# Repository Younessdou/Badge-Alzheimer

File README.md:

# Badge-Alzheimer
Projet électronique du semestre 5

# Sommaire 
### Introduction
### I) Cahier des charges
### II) Gantt et diagramme d'architecture
### III) Choix des composants
##### A) Module GPS
##### B) Module Lora
##### C) Microprocesseur
### IV) Réalisation du PCB
##### A) Choix des pins du microP
##### B) Schématic & board
##### C) Soudage des composants sur la carte
### V) Codage du module GPS 
### VI) LoRa
### VII) Alimentation
### Conclusion

# Remerciement
Nous remercions nos tuteurs durant ce projet Mr.Papazoglou et Mme.Giannini pour leurs conseils et astuces qui nous ont permis de découvrir de nouvelles choses et acquérir de nouvelles compétences tout en appliquant ce que nous avions vu durant cette année d'étude, et nous tenons aussi à remercier Mme. Kittel du bureau technique qui nous a aidé pour notre PCB.
# Introduction
Dans le cadre des projets tutorés du semestre 6, nous avons été amenés à travailler sur la conception d’un badge Alzheimer qu’on a choisi de le nommer «TrackNanny».
TrackNanny est tout simplement un outil de localisation et de prévention, destiné aux personnes atteintes d’Alzheimer ou aux personnes qu’on ne souhaiterait pas perdre à l’extérieur. Ce badge permet d’envoyer une alerte à la personne qui prend en charge l’utilisateur dès que ce dernier dépasse un rayon prédéfini par rapport à un épicentre qui est aussi prédéfini. Ce badge contient aussi un bouton SOS qui permet d’envoyer un autre message d’alerte avec la position exacte de l’utilisateur si quelqu’un l’a trouvé.
Pour notre projet on a pris l'adresse de l'ENSEA comme épicentre et on a défini un rayon de 700m.       
    <p align="center">
  
### Gantt & diagramme d’architecture
Durant ces 11 séances de projets, nous avons commencé par répartir les tâches entres nous en remplissant notre diagramme de Gantt où on a placé nos missions par ordre de priorité.

Et on a structuré notre projet selon le diagramme d'architecture suivant:

# I) Cahier des charges
Pendant la première séance nous avons commencé par établir un cahier des charges sur lequel on s'est basé pour la suite du projet:
    <p align="center">

    Budget: 50€
# III) Choix des composants
### A) Module GPS
      Module GPS : SKU:TEL0132

 ### B) Module LORA
   Module LoRa-E5 Grove 113020091\

On a choisi le module LoRa-E5 Grove 113020091 puisque c'était le moins cher et le plus compacte par rapport aux autres.
  
 ### C) Microprocesseur
     STM32L412KBT6

tableau des microprocesseurs proposés:

  Au début on avait le choix entre 4 microprocesseurs, et puisqu’on va utiliser 2 UART et 1 GPIO; 1 pour le module GPS et 1 pour le LoRa, donc il nous restait 2 choix et puisque le STM32L021K4T6 n'est pas toujours fiable , on a opté pour le 4ème vu son prix qui est presque la moitié du 3ème et aussi puisqu’il a le même package que les autres donc on aura la possibilité de le changer sur notre PCB et aussi puisqu’il contient que 32 pin et ça reste plus simple et facile à souder et manipuler que celui avec 64 pins.

# IV) Réalisation du PCB
        
 ### A) Choix des pins du microP
Nous avons fait bon usage du Logiciel STM32CubeIDE afin de voir les pins associés à l’UART, leurs numéros ainsi que leurs dispositions lors de la création de la carte Pcb.
Après ajout des pins pour notre bouton SOS et RESET, on se retrouve avec une Pin view comme ci-contre :

- Pin PA2-3 : Module GPS
- Pin PA5 : Bouton SOS
- Pin PA14-15 : RESET 
- Pin PA9-10 : Module LoRaWan   
        
 ### B) Schematic et board
 
 Nous avons commencé par créer notre PCB sur eagle en téléchargeant les librairies contenant nos composants, puis on a créé notre schématic qui contient la partie microP, l'alimentation les connecteurs pour le module GPS et LoRa ainsi que nos deux boutons reset et SOS.

  À partir de ce schématic on a généré notre board pour relier les composants entre eux en top ou en buttom.

  Après le routage de ce dernier, on a bien respecté notre objectif qui est de réduire l'espace entre les composants et mettre un grand nombre de liaison en top afin d'obtenir une carte adéquate avec la forme de notre badge, ensuite on l'a imprimé et on a soudé les composants dessus à l'aide de mr.Papazouglou et mme.Kittel.
 
 Voici le format final de notre PCB:

 # V) Codage du module GPS
 Cette partie a été faite par deux autres étudiants; Alexis Regnault et Valérian PRIOU qui se sont occupés de la partie software de plusieurs projets dont le nôtre, veuillez trouver leurs rapports pour notre projet ci-joint avec les fichiers, il est intitulé «Rapport_Alzheimer_PRIOU_REGNAULT.pdf» ainsi que le git du codage du module GPS via le lien ci-dessous.
https://github.com/ValerianPRIOU/Alzheimer
        
 # VI) LoRa or LoRaWAN?
 Cette partie a été géré par deux autres étudiants; Mohamed Amine Bouhyat Oliver BELLIARD ABREU, ils ont aussi travaillé sur la partie LoRawan des autres projets. Veuillez trouver le lien de leurs git ci-dessous.
        
  https://github.com/OliverBELLIARD/LoRaWAN     

 # VII) Alimentation:
 Cette partie a été géré par deux étudiantes; Inass Rachidi Manon COTTAR qui s'occupaient de l'alimentation de plusieurs projets en même temps, vous trouverez le lien ci-dessous du travail détaillé qui a été fait en parallèle avec nous.

https://github.com/inassra/batterie

# Conclusion
Pour le moment, nous n'avons toujours pas terminé notre projet, il nous reste dans la partie software l'assemblage du code du module GPS et le module LoRa dans un seul code qui doit être implémenter par la suite dans le microprocesseur, lors du test de notre carte on a eu un problème avec le régulateur qui délivre les 5V en revanche on obtient bien nos 6V à l'entrée ainsi que nos 3,3V à la sortie de l'autre régulateur. Ce premier projet a été très intéressant puisqu'on a pu appliquer la plupart des connaissances et compétences vu durant cette année. L'idée du projet est très intéressante et on peut poursuivre le travail sur ce projet après en essayant de le compléter et de l'améliorer en modifiant notre cahier des charges et en ajoutant d'autres missions comme un accéléromètre pour détecter la chute de l'utilisateur.

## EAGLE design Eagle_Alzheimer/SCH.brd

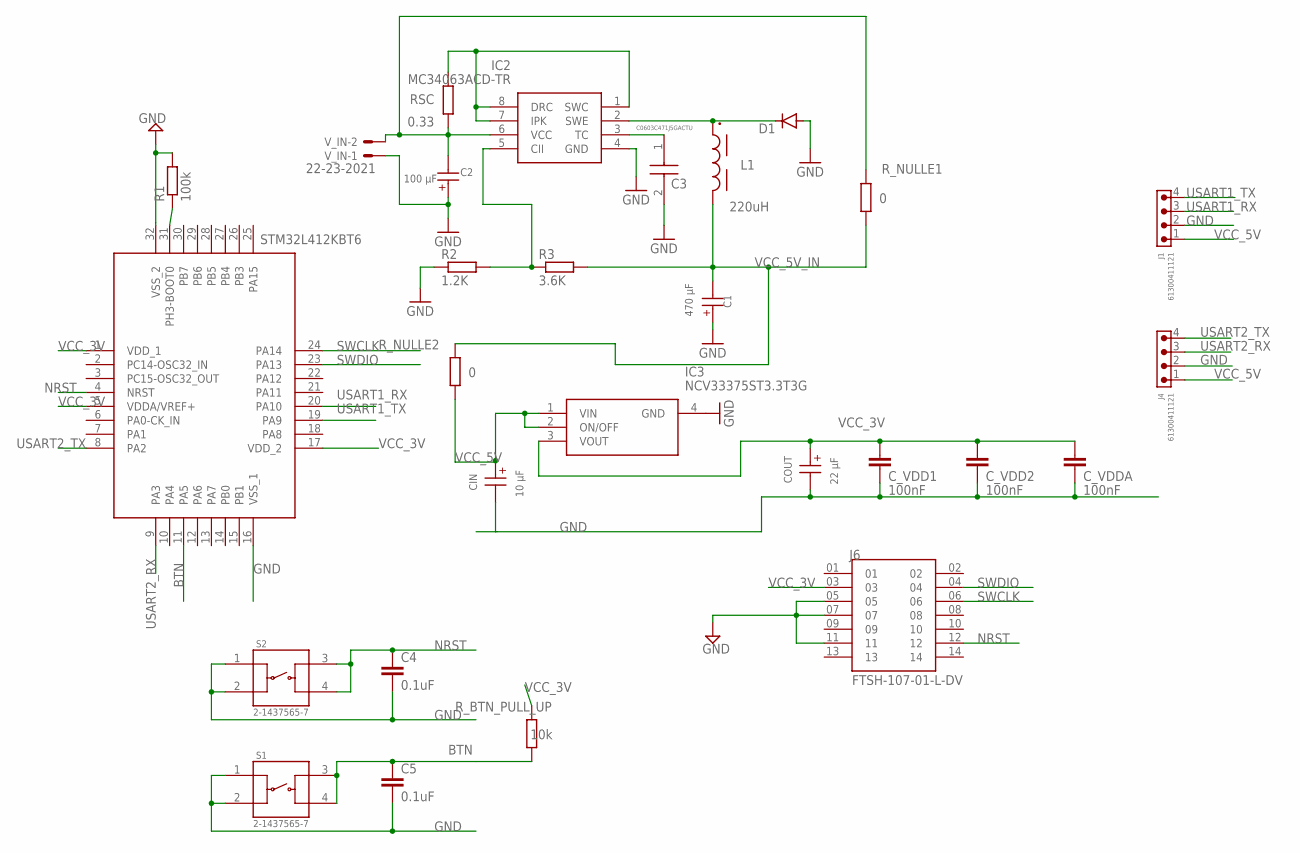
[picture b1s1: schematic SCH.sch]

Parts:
C1: 470 µF; WCAP-ASLL_8X10.5(DXL)
C2: 100 µF; WCAP-ASLL_6.3X7.7(DXL)
C3: C0603C471J5GACTU; C0603
C4, C5: 0.1uF; C0603
CIN: 10 µF; WCAP-ASLL_4X5.5(DXL)
COUT: 22 µF; WCAP-ASLL_5X5.5(DXL)
C_VDD1, C_VDD2: 100nF; C0603
C_VDDA: 100nF; C0603
D1: DIODE-DO214AC; DO214AC
IC1: STM32L412KBT6; QFP80P900X900X160-32N
IC2: MC34063ACD-TR; SOIC127P600X175-8N
IC3: NCV33375ST3.3T3G; SOT230P700X175-4N
J1, J4: 61300411121
J6: FTSH-107-01-L-DV; SAMTEC_FTSH-107-01-L-DV
L1: 220uH; WE-PDA_1260
R1: 100k; R0603
R2: 1.2K; R0603
R3: 3.6K; R0603
RSC: 0.33; R1206W
R_BTN_PULL_UP: 10k; R0603
R_NULLE1, R_NULLE2: 0; R0603
S1, S2: 2-1437565-7; SW_2-1437565-7
V_IN: 22-23-2021

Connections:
BTN: C5.1, IC1.11 (PA5), R_BTN_PULL_UP.1, S1.3, S1.4
GND: C1.1 (+), C2.1 (+), C3.2, C4.2, C5.2, CIN.2 (-), COUT.2 (-), C_VDD1.2, C_VDD2.2, C_VDDA.2, D1.A, IC1.16 (VSS_1), IC1.32 (VSS_2), IC2.4 (GND), IC3.4 (GND), J1.2, J4.2, J6.05, J6.07, J6.11, R1.2, R2.1, S1.1, S1.2, S2.1, S2.2, V_IN.1
unnamed: IC1.31 (PH3-BOOT0), R1.1
unnamed: IC2.1 (SWC), IC2.7 (IPK), IC2.8 (DRC), RSC.2
unnamed: IC2.5 (CII), R2.2, R3.1
unnamed: C3.1, IC2.3 (TC)
unnamed: D1.C, IC2.2 (SWE), L1.1
NRST: C4.1, IC1.4 (NRST), J6.12, S2.3, S2.4
SWCLK: IC1.24 (PA14), J6.06
SWDIO: IC1.23 (PA13), J6.04
USART1_RX: IC1.20 (PA10), J1.3
USART1_TX: IC1.19 (PA9), J1.4
USART2_RX: IC1.9 (PA3), J4.3
USART2_TX: IC1.8 (PA2), J4.4
VCC_3V: COUT.1 (+), C_VDD1.1, C_VDD2.1, C_VDDA.1, IC1.1 (VDD_1), IC1.5 (VDDA/VREF+), IC1.17 (VDD_2), IC3.3 (VOUT), J6.03, R_BTN_PULL_UP.2
VCC_5V: CIN.1 (+), IC3.1 (VIN), IC3.2 (ON/OFF), J1.1, J4.1, R_NULLE2.1
VCC_5V_IN: C1.2 (-), L1.2, R3.2, R_NULLE1.1, R_NULLE2.2
VCC_6V: C2.2 (-), IC2.6 (VCC), RSC.1, R_NULLE1.2, V_IN.2

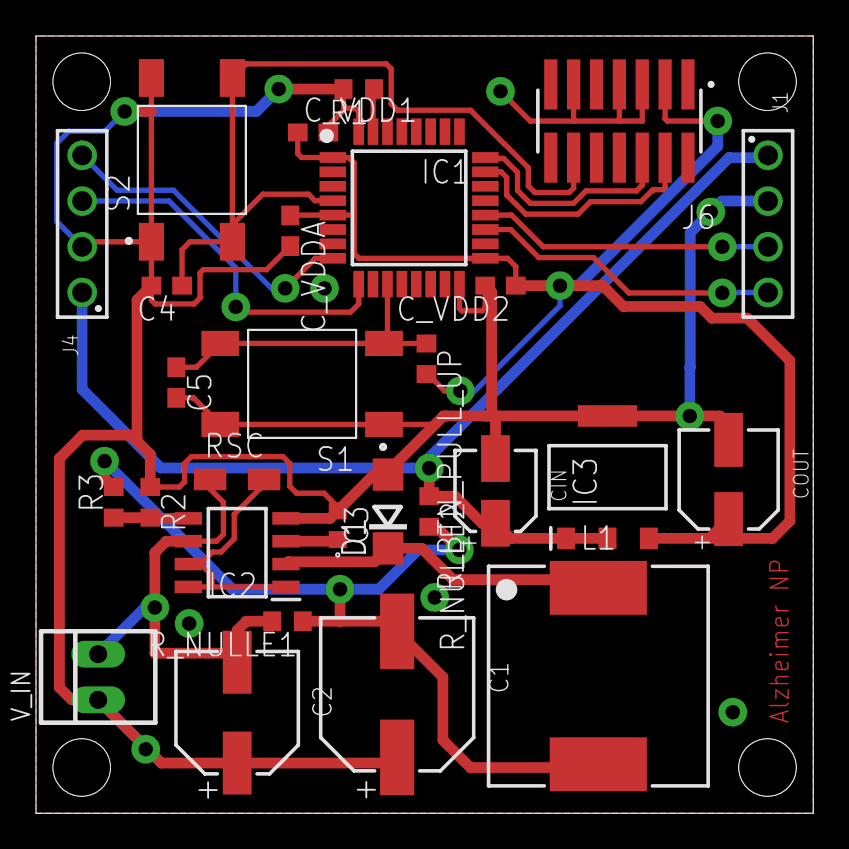
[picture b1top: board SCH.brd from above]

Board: 2 copper layers, 43.2 x 43.2 mm, 28 parts (0 on the bottom side), 18 nets.

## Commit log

2022-06-06 Ajout du compte rendu partie capteurs
2022-06-06 Create Eagle

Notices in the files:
parts and their libraries:
C1: Copyright: Würth Elektronik
